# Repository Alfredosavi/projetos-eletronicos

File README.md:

# Projetos Eletrônicos

## :page_facing_up:	Projetos
  1. [Testador de foto acoplador](./OptoCouplerTester/): Testador de foto acoplador para sockets de `4-PIN e 6-PIN`;
  2. [Amplificador classe AB](./AmplificadorClasseAB/): Amplificador classe AB de 20W.
  
`OBS`: Para mais informações, acesse o arquivo `readme` de cada projeto.

## 🔥 Schematics e Layouts
Verifique no arquivo `readme` de cada projeto para mais informações.

## ⚡️ Como contribuir

- Faça um fork desse repositório;
- Cria uma branch com a sua feature: `git checkout -b minha-feature`;
- Faça commit das suas alterações: `git commit -m 'feat: Minha nova feature'`;
- Faça push para a sua branch: `git push origin minha-feature`.

Depois que o merge da sua pull request for feito, você pode deletar a sua branch.

## :memo: Licença

Esse projeto está sob a licença MIT. Veja o arquivo [LICENSE](LICENSE) para mais detalhes.

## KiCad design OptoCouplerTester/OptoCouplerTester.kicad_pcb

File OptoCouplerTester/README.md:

# OptoCouplerTester

Um teste fácil e rápido para acopladores ópticos, com opção para sockets de 4 ou 8 pinos.

`OBS:` Utilizado uma tensão de 9V para acionar a maioria dos acopladores. Na PCI foi colocado `duas` formas de _input_: JACK P4 ou barra de pinos. 

Após colocar o foto acoplador no socket (verificar polaridade), acionar o botão `TEST`. Se o LED acender indica que o acoplador está bom. 

## :zap: Esquemático

## :fire: Layout

PCI             |  Visão 3D
:--------------:|:--------------:
  |  

## :hammer: Software utilizado
* [Kicad 6](https://www.kicad.org/)

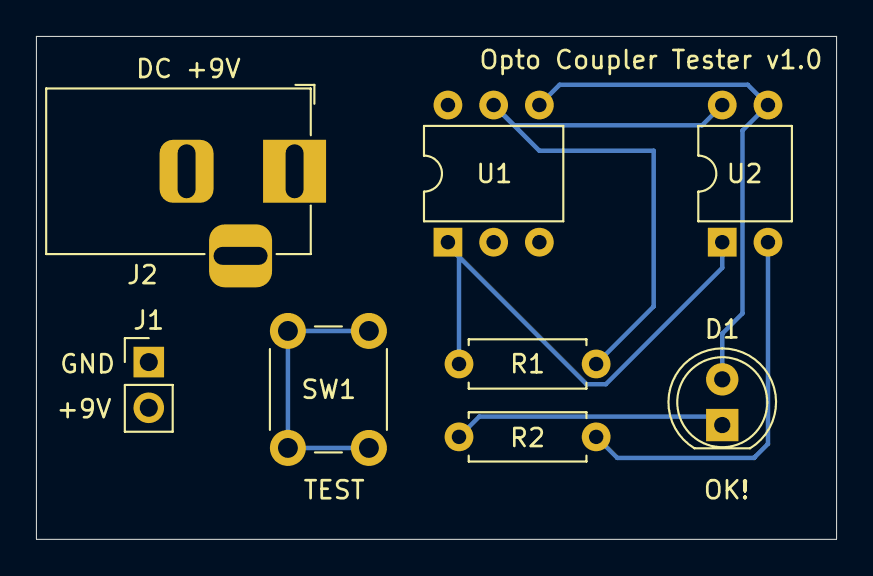
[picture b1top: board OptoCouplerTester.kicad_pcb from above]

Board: 2 copper layers, 44.5 x 27.9 mm, 8 parts (0 on the bottom side), 6 nets.

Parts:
D1: LED; LED_D5.0mm
J1: BAT; PinHeader_1x02_P2.54mm_Vertical
J2: JACK P4; BarrelJack_Horizontal
R1: 1k; R_Axial_DIN0207_L6.3mm_D2.5mm_P7.62mm_Horizontal
R2: 220R; R_Axial_DIN0207_L6.3mm_D2.5mm_P7.62mm_Horizontal
SW1: button; SW_PUSH_6mm_H8mm
U1: 4N25; DIP-6_W7.62mm
U2: PC817; DIP-4_W7.62mm

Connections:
+9V: J1.1, J2.1, SW1.1 (A), SW1.2 (A)
GND: J1.2, J2.2, R2.2, U1.2, U2.2
unnamed: D1.1 (K), R2.1
unnamed: D1.2 (A), U1.4, U2.3
unnamed: R1.1, U1.1, U2.1
unnamed: R1.2, U1.5, U2.4

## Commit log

2022-03-22 feat: Add OptoCouplerTester
2022-03-22 Create LICENSE
2022-05-16 feat: Add readme, simulation and project kicad layout
